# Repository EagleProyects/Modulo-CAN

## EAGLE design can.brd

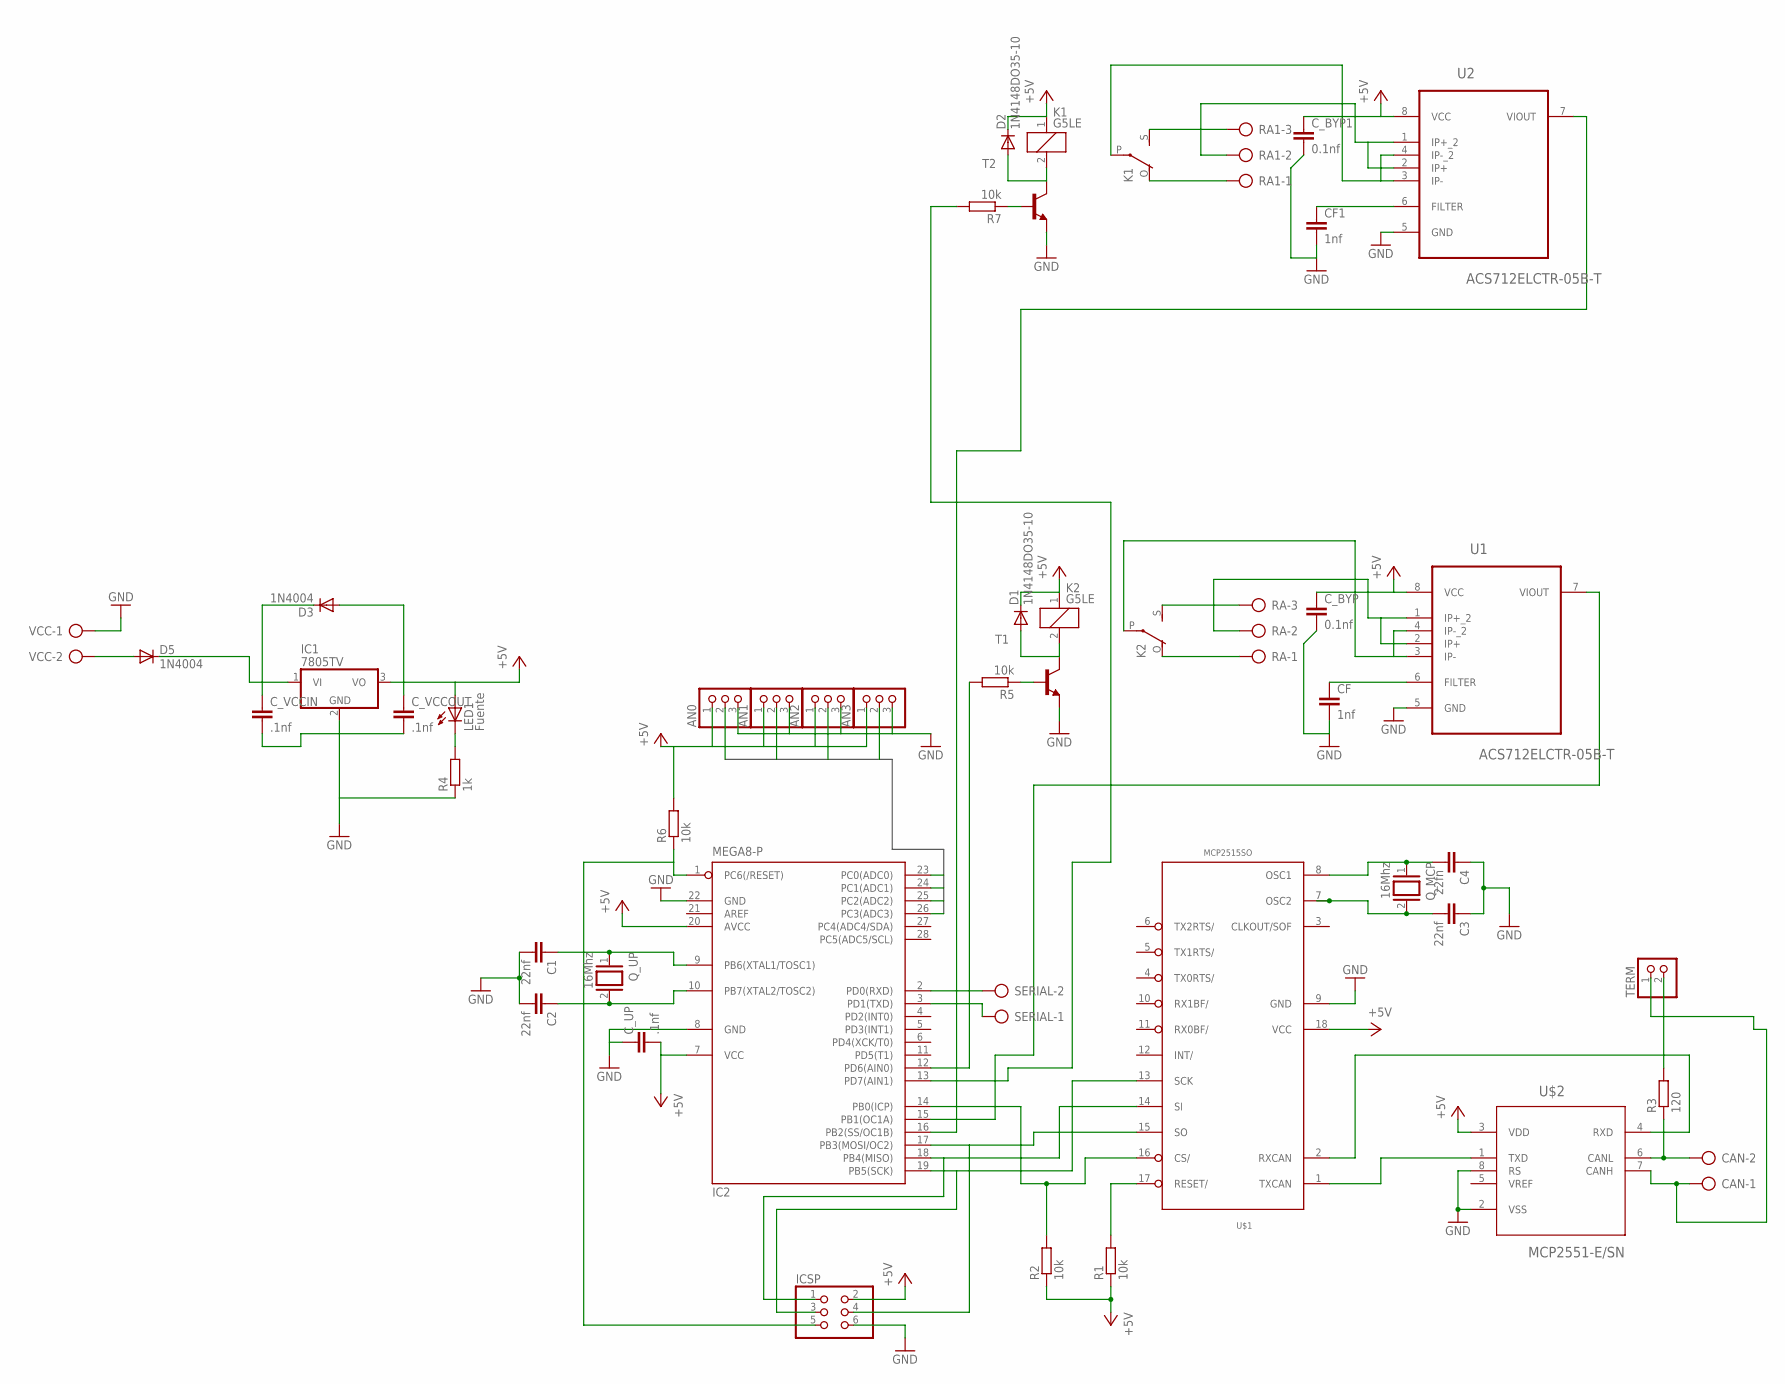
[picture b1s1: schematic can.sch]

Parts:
AN0, AN1, AN2, AN3: PINHD-1X3; 1X03
C1, C2, C3: 22nf; C025-025X050
C4: 22fn; C025-025X050
CAN: AK500/2
CF, CF1: 1nf; C025-025X050
C_BYP, C_BYP1: 0.1nf; C025-025X050
C_UP: .1nf; C025-025X050
C_VCCIN: .1nf; C025-025X050
C_VCCOUT: .1nf; C025-025X050
D1, D2: 1N4148DO35-10; DO35-10
D3, D5: 1N4004; DO41-10
IC1: 7805TV; TO220V
IC2: MEGA8-P; DIL28-3
ICSP: PINHD-2X3; 2X03
K1, K2: G5LE
LED1: Fuente; LED3MM
Q_MCP: 16Mhz; QS
Q_UP: 16Mhz; QS
R1, R2, R5, R6, R7: 10k; 0207/10
R3: 120; 0207/10
R4: 1k; 0207/10
RA, RA1: AK500/3
SERIAL: AK500/2
T1, T2: BC548-NPN-TO92-CBE; TO92-CBE
TERM: PINHD-1X2; 1X02
U1, U2: ACS712ELCTR-05B-T; SOIC127P600X175-8N
U$1: MCP2515SO; SO18L
U$2: MCP2551-E/SN; SOIC127P600X175-8N
VCC: AK500/2

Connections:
B0: AN0.2, IC2.23 (PC0(ADC0))
B1: AN1.2, IC2.24 (PC1(ADC1))
B2: AN2.2, IC2.25 (PC2(ADC2))
B3: AN3.2, IC2.26 (PC3(ADC3))
GND: AN0.3, AN1.3, AN2.3, AN3.3, C1.2, C2.2, C3.1, C4.1, CF.2, CF1.2, C_BYP.2, C_BYP1.2, C_UP.1, C_VCCIN.2, C_VCCOUT.2, IC1.2 (GND), IC2.8 (GND), IC2.22 (GND), ICSP.6, R4.1, T1.E, T2.E, U1.5 (GND), U2.5 (GND), U$1.9 (GND), U$2.2 (VSS), U$2.8 (RS), VCC.1
unnamed: C1.1, IC2.9 (PB6(XTAL1/TOSC1)), Q_UP.1
unnamed: C2.1, IC2.10 (PB7(XTAL2/TOSC2)), Q_UP.2
unnamed: IC2.17 (PB3(MOSI/OC2)), ICSP.4, U$1.15 (SO)
unnamed: IC2.14 (PB0(ICP)), R2.2, U$1.16 (CS/)
unnamed: CAN.2, R3.1, U$2.6 (CANL)
unnamed: IC2.16 (PB2(SS/OC1B)), U2.7 (VIOUT)
unnamed: IC2.19 (PB5(SCK)), ICSP.3, U$1.13 (SCK)
unnamed: C4.2, Q_MCP.1, U$1.8 (OSC1)
unnamed: C3.2, Q_MCP.2, U$1.7 (OSC2)
unnamed: D1.A, K2.2, T1.C
unnamed: U$1.1 (TXCAN), U$2.1 (TXD)
unnamed: U$1.2 (RXCAN), U$2.4 (RXD)
unnamed: R1.2, U$1.17 (RESET/)
unnamed: CAN.1, TERM.1, U$2.7 (CANH)
unnamed: R3.2, TERM.2
unnamed: R5.1, T1.B
unnamed: LED1.K (C), R4.2
unnamed: RA.2, U1.1 (IP+_2), U1.2 (IP+)
unnamed: K2.O, RA.1
unnamed: K2.S, RA.3
unnamed: IC2.1 (PC6(/RESET)), ICSP.5, R6.1
unnamed: IC2.2 (PD0(RXD)), SERIAL.2
unnamed: IC2.3 (PD1(TXD)), SERIAL.1
unnamed: IC2.12 (PD6(AIN0)), R5.2
unnamed: IC2.15 (PB1(OC1A)), U1.7 (VIOUT)
unnamed: CF.1, U1.6 (FILTER)
unnamed: K2.P, U1.3 (IP-), U1.4 (IP-_2)
unnamed: D2.A, K1.2, T2.C
unnamed: D5.A, VCC.2
unnamed: R7.1, T2.B
unnamed: K1.O, RA1.1
unnamed: K1.S, RA1.3
unnamed: IC2.13 (PD7(AIN1)), R7.2
unnamed: K1.P, U2.3 (IP-), U2.4 (IP-_2)
unnamed: RA1.2, U2.1 (IP+_2), U2.2 (IP+)
unnamed: CF1.1, U2.6 (FILTER)
unnamed: IC2.18 (PB4(MISO)), ICSP.1, U$1.14 (SI)
unnamed: C_VCCIN.1, D3.C, D5.C, IC1.1 (VI)
VCC: AN0.1, AN1.1, AN2.1, AN3.1, C_BYP.1, C_BYP1.1, C_UP.2, C_VCCOUT.1, D1.C, D2.C, D3.A, IC1.3 (VO), IC2.7 (VCC), IC2.20 (AVCC), ICSP.2, K1.1, K2.1, LED1.A, R1.1, R2.1, R6.2, U1.8 (VCC), U2.8 (VCC), U$1.18 (VCC), U$2.3 (VDD)

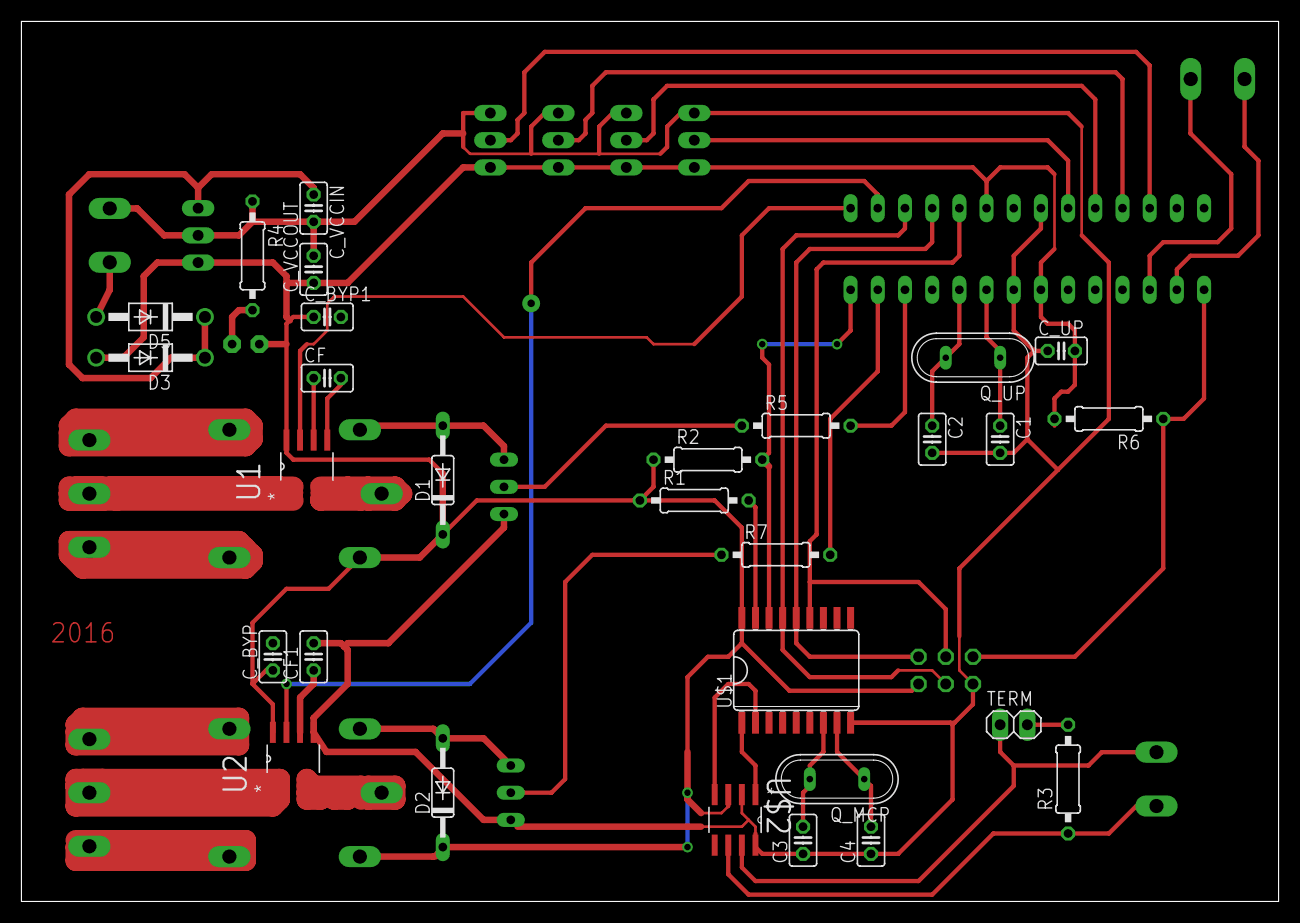
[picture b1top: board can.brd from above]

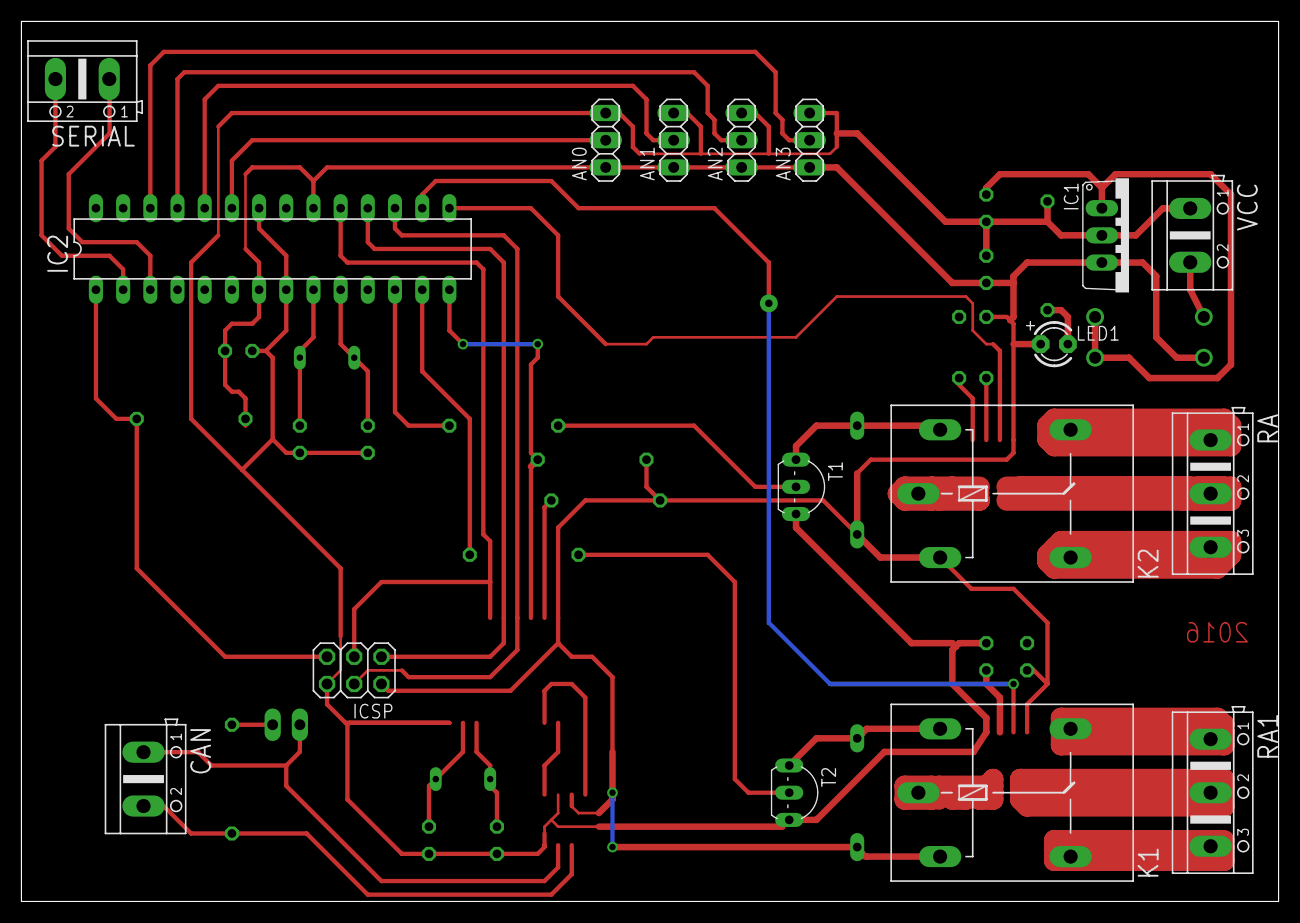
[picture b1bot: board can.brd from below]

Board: 2 copper layers, 117.5 x 82.2 mm, 46 parts (17 on the bottom side), 44 nets.

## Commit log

2016-02-17 :octocat: Added .gitattributes & .gitignore files
2016-02-17 sewasr
2016-04-29 fix
    sfdsa
2016-04-29 se creo el archivo board
